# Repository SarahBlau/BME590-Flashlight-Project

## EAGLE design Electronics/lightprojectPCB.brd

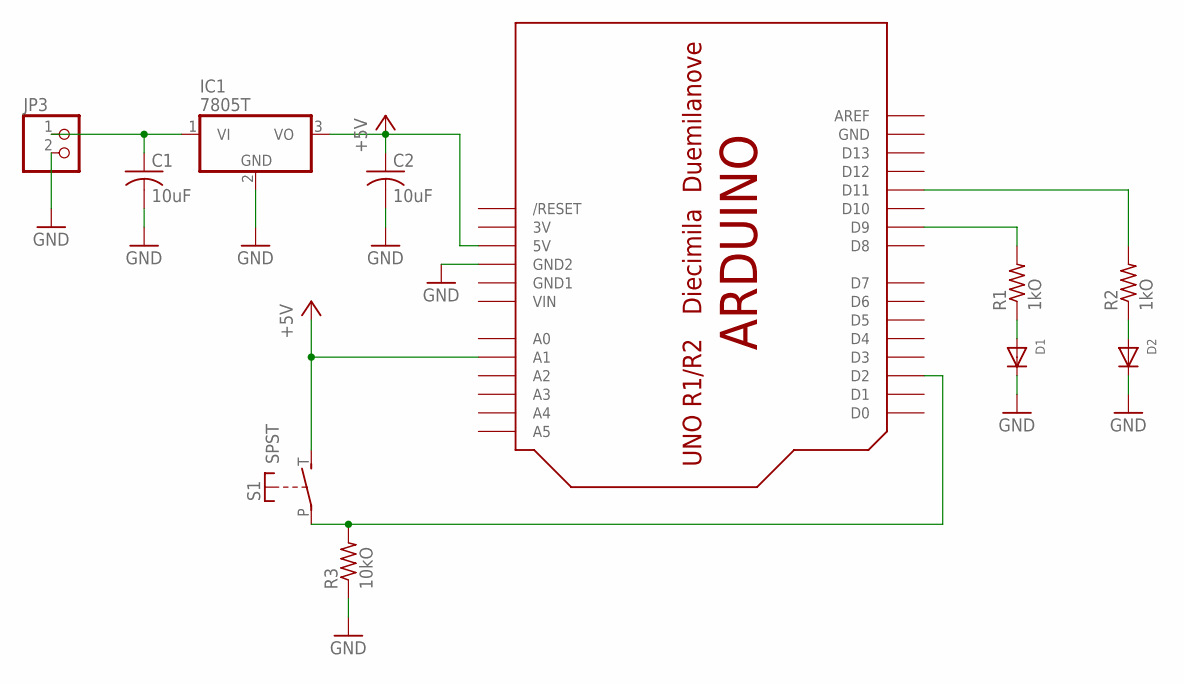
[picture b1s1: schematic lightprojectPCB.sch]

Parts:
C1, C2: 10uF; C0805
D1, D2: DIODESMA; SMADIODE
IC1: 7805T; TO220H
JP3: PINHD-1X2; 1X02
R1, R2: 1kO; M0805
R3: 10kO; M0805
S1: SPST; JUDCOSPST
U$1: ARDUINO-BPLACE

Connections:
3V: U$1.3V
+5V: C2.1, IC1.3 (VO), S1.T (S), U$1.5V, U$1.A1
GND: C1.2, C2.2, D1.C, D2.C, IC1.2 (GND), JP3.2, R3.1, U$1.GND, U$1.GND2
GND1: U$1.GND1
unnamed: R1.2, U$1.D9
unnamed: C1.1, IC1.1 (VI), JP3.1
unnamed: D2.A, R2.1
unnamed: D1.A, R1.1
unnamed: R3.2, S1.P, U$1.D2
unnamed: R2.2, U$1.D11
VIN: U$1.VIN

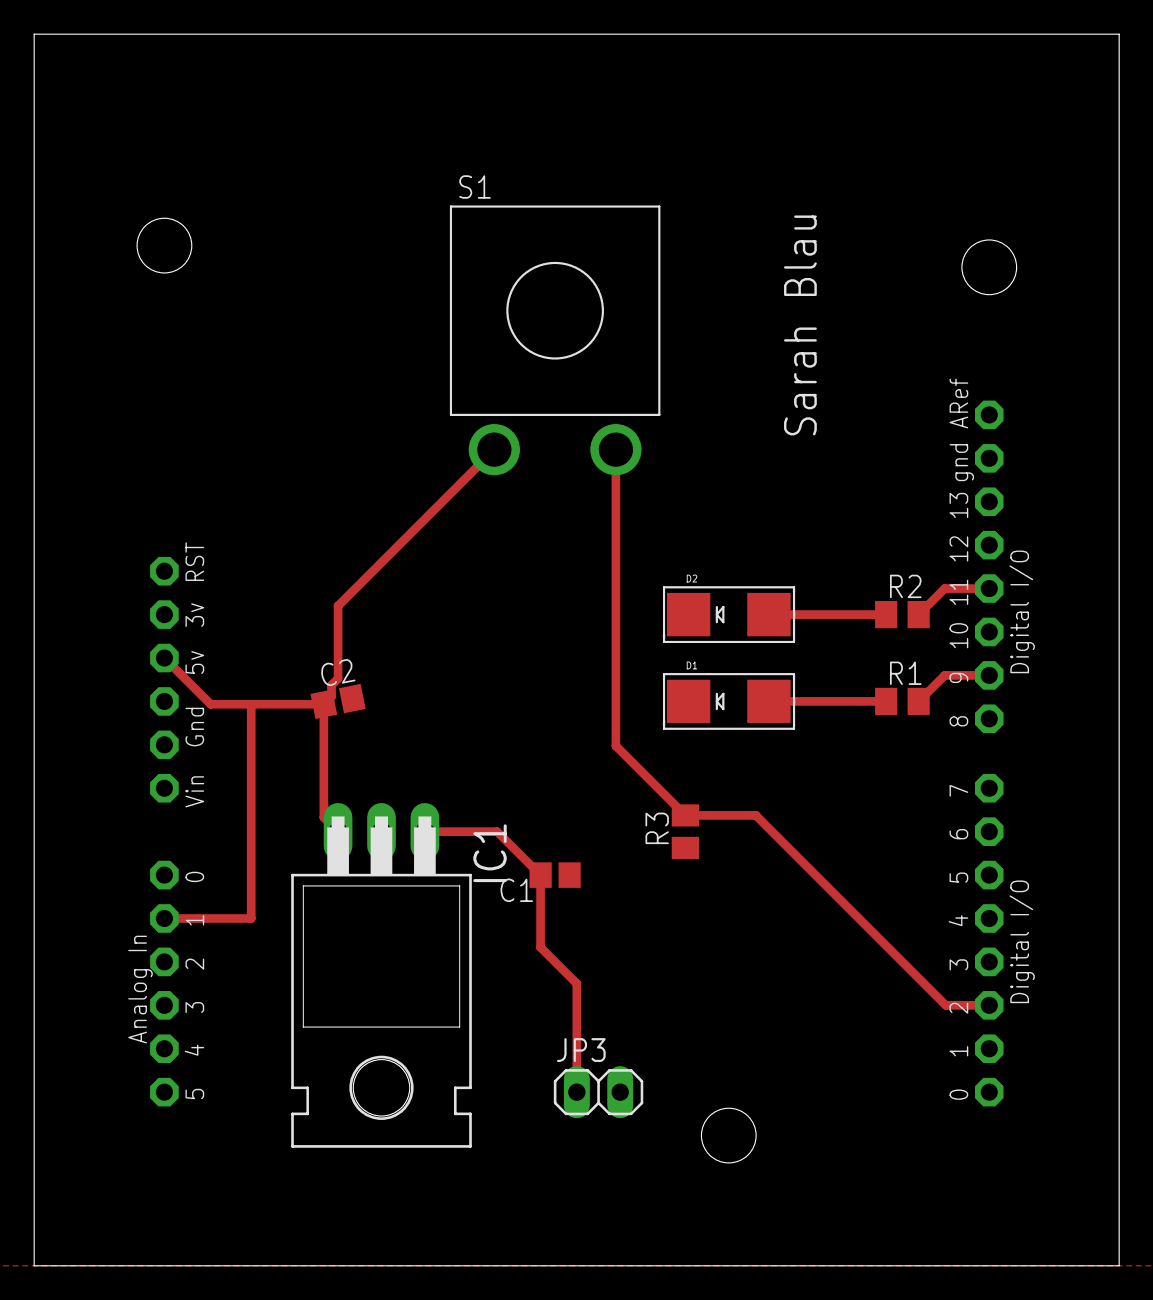
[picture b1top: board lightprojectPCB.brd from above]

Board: 2 copper layers, 63.5 x 72.1 mm, 11 parts (0 on the bottom side), 8 nets.

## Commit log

2018-11-01 Create making directory
2018-11-01 Add files via upload
    handwritten draft of schematic
2018-11-01 Add files via upload
    Handwritten flowchart
2018-11-08 Add files via upload
    First PDFs of ECAD schematic and PCB
2018-11-12 Add files via upload
    Original ECAD files (ie not PDFs)
2018-11-24 Add files via upload
    Bare minimum code with debouncing but no battery life reading
2018-11-24 Add files via upload
    Updated schematic with Arduino footprint
2018-11-26 Add files via upload
    Updated PCB, but need to redo polygon pour
2018-11-26 Add files via upload
    Updated schematic and board to include an analog read of the battery voltage - still need to address polygon pour and make sure there are appropriate components in the lab for my design
2018-11-26 Add files via upload
    Added battery read and display functionality
2018-11-27 Add files via upload
    Moved board back to origin, should be finalized
2018-11-28 Add files via upload
    A very basic box
2018-11-30 Add files via upload
    Shortened the board so it wouldn't hang over the Arduino on the edge where I need the ports to be accessible
2018-11-30 Add files via upload
    Shortened box, added holes for power and USB
2018-12-05 Add files via upload
    Corrected box and button extender
2018-12-05 Add files via upload
    Improved debounce, fixed battery detection
2018-12-06 Add files via upload
    Fixed lip for putting lid on
2018-12-09 Add files via upload
    Longer box, deeper lid, started new attachment
2018-12-09 Add files via upload
    Fixed debouncing
2018-12-11 Add files via upload
    Breadboard working
2018-12-11 Add files via upload
    Battery concept works
2018-12-11 Add files via upload
    PCB soldered correctly
